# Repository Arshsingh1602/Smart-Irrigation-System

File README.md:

# Smart Irrigation System using LoRa and ESP32

This project is a transmitter-receiver duo using the LoRa communication protocol that helps us to revolutionize the agriculture industry by advancing the Smart Irrigation System. The transmitter acts as the node that transmits the data, and the receiver acts as the central node to receive that data and communicate it further, and process it.

Features of the project include: 
  1. Soil Moisture Detection
  2. Temperature and Humidity Detection
  3. Transmission (Long Range(upto 12-15km in rural areas))
  4. External parameters fetching, calculations, and predictions based on ML models
  5. Response to outcomes makes it a two-way system without human intervention.

| Component                 | Quantity | Description / Link         |
|---------------------------|----------|-----------------------------|
| ESP32 Dev Board           | 2        | WiFi + Bluetooth enabled    |
| SX1278 LoRa Module        | 2        | 433MHz                     |
| Soil Moisture Sensor      | 1        | Capacitive type            |
| MCP9808 Temp Sensor/DHT11 | 1        | Temperature sensor         |
| Water Valve (12V)         | 1        | Controlled via relay       |
| Relay Module              | 1        | For switching valve        |
| Power Supply (12V, 5V)    | 1 each   | For sensors and motors     |

To understand how the project works, we must understand some things first:

Soil Moisture Content: The amount of water present in the soil, usually measured as a percentage. It can be volumetric (by volume) or gravimetric (by weight).
Field Capacity (FC): The maximum moisture level that soil retains after excess water has drained. It represents the ideal moisture for plant growth.
Wilting Point (WP): The minimum moisture level at which plants begin to wilt due to lack of available water.
Permanent Wilting Point (PWP): A critical level where plants can no longer recover, even if water is reintroduced.
Available Water Content (AWC): The difference between field capacity and wilting point. It indicates the water range that plants can effectively use.

AWC = Field Capacity − Wilting Point

Saturation Point: When all soil pores are filled with water. Beyond this point, water drainage occurs, and root oxygen is limited.
Soil Water Potential (Tension): Indicates how tightly water is held in soil. Measured in kPa, where:

0 kPa = Saturated soil

−33 kPa ≈ Field capacity

−1500 kPa ≈ Wilting point

Soil Texture: Affects water retention. Sandy soils drain quickly, while clay holds more water.

The soil moisture sensor in the transmitter checks the water content in the soil, sends analogue data to the ESP 32, which takes the analogue data and converts it to scientifically accurate values and parameters. These parameters are defined above. There are various ways to program out AI/ML to find out what equation best fits the analogue data, which can be calculated based on heavy experimentation and data collection. The temperature sensor also sends its data to the ESP, and from there, the microcontroller takes the help of the LoRa module to transmit that data to the receiver that is kept far away from the transmitter. The main motto for this transmission is to have data collection and transmission from places in the field where the is no internet connection. One receiver can handle multiple transmitters varying from 4-10(max).

The receiver side is connected to the internet with wifi and can receive the transmitter data, and with the help of an internet connection, sends data to the cloud server that stores data according to the transmitter number, for further analysis. The main role of the receiver is to upload the transmitter's data and also send the data from the cloud back to the respective transmitters in order to control the relay, which controls the valve for irrigation. 

The ML model takes the temperature data and the soil moisture sensor, combined with the local humidity and rainfall fetched from the API. The model predicts when to command the specific valve to turn on, depending on the future rainfall predictions and the current status of the soil moisture. For example, if the soil moisture is below the critical level, then the part of the land should be irrigated immediately. But if the soil moisture is low, but the algorithm predicts that rainfall is expected in a few days, then, depending upon the average evaporation rate and the humidity, only a specific amount of water will be released such that the rainfall replenishes the remaining required amount. This way it saves water.

1. Connect all hardware as per the schematic.
2. Flash "sender.ino" to field ESP32.
3. Flash "receiver.ino" to the base ESP32.
4. Add your Firebase details to "firebase_config.h.h".
5. Power up both ESP32 boards.

Dependencies / Libraries:
- "Firebase_ESP_Client"
- "LoRa by Sandeep Mistry"

Challenges: 
  1. LoRa supports distances up to 15-20km in rural areas, but sometimes fields are larger than that.
  2. Theoretically, one transmitter can cover an area of 250 m^2, but this sample space technique that we assumed here only works for flat land.
  3. Configuring the patch of transmitters if farmers grow different types of crops on different patches of their land is difficult, as one crop can be selected but cannot select multiple crops.
  4. The single transmitter cannot handle so much data at the exact same time and will not upload correct data if we do so.

Future Scope:
  1. The individual transmitters can be coded as nodes of a mesh that can act like nodes that bounce/propel data forward if the distance between any transmitter and the receiver is too long.
  2. The receiver can be coded to generate a sequence of data received, store locally just for the purpose of uploading it to the server(forming a queue structure with the FIFO principle). This way, we can handle a huge amount of load on the receiver and avoid data corruption or system failure.
  3. Solar panels can be installed on each transmitter to make it self-sufficient.
  4. An algorithm can be developed that takes satellite images of the land from the maps API and analyzes the area based on terrain and slope, and finds the best locations to place our transmitters strategically to cover the whole field.

This is a public repo licensed under the MIT license. Users are obliged to reference/credit me(Arsh Singh) when copying the project or using/updating this project.

Made by Arsh Singh

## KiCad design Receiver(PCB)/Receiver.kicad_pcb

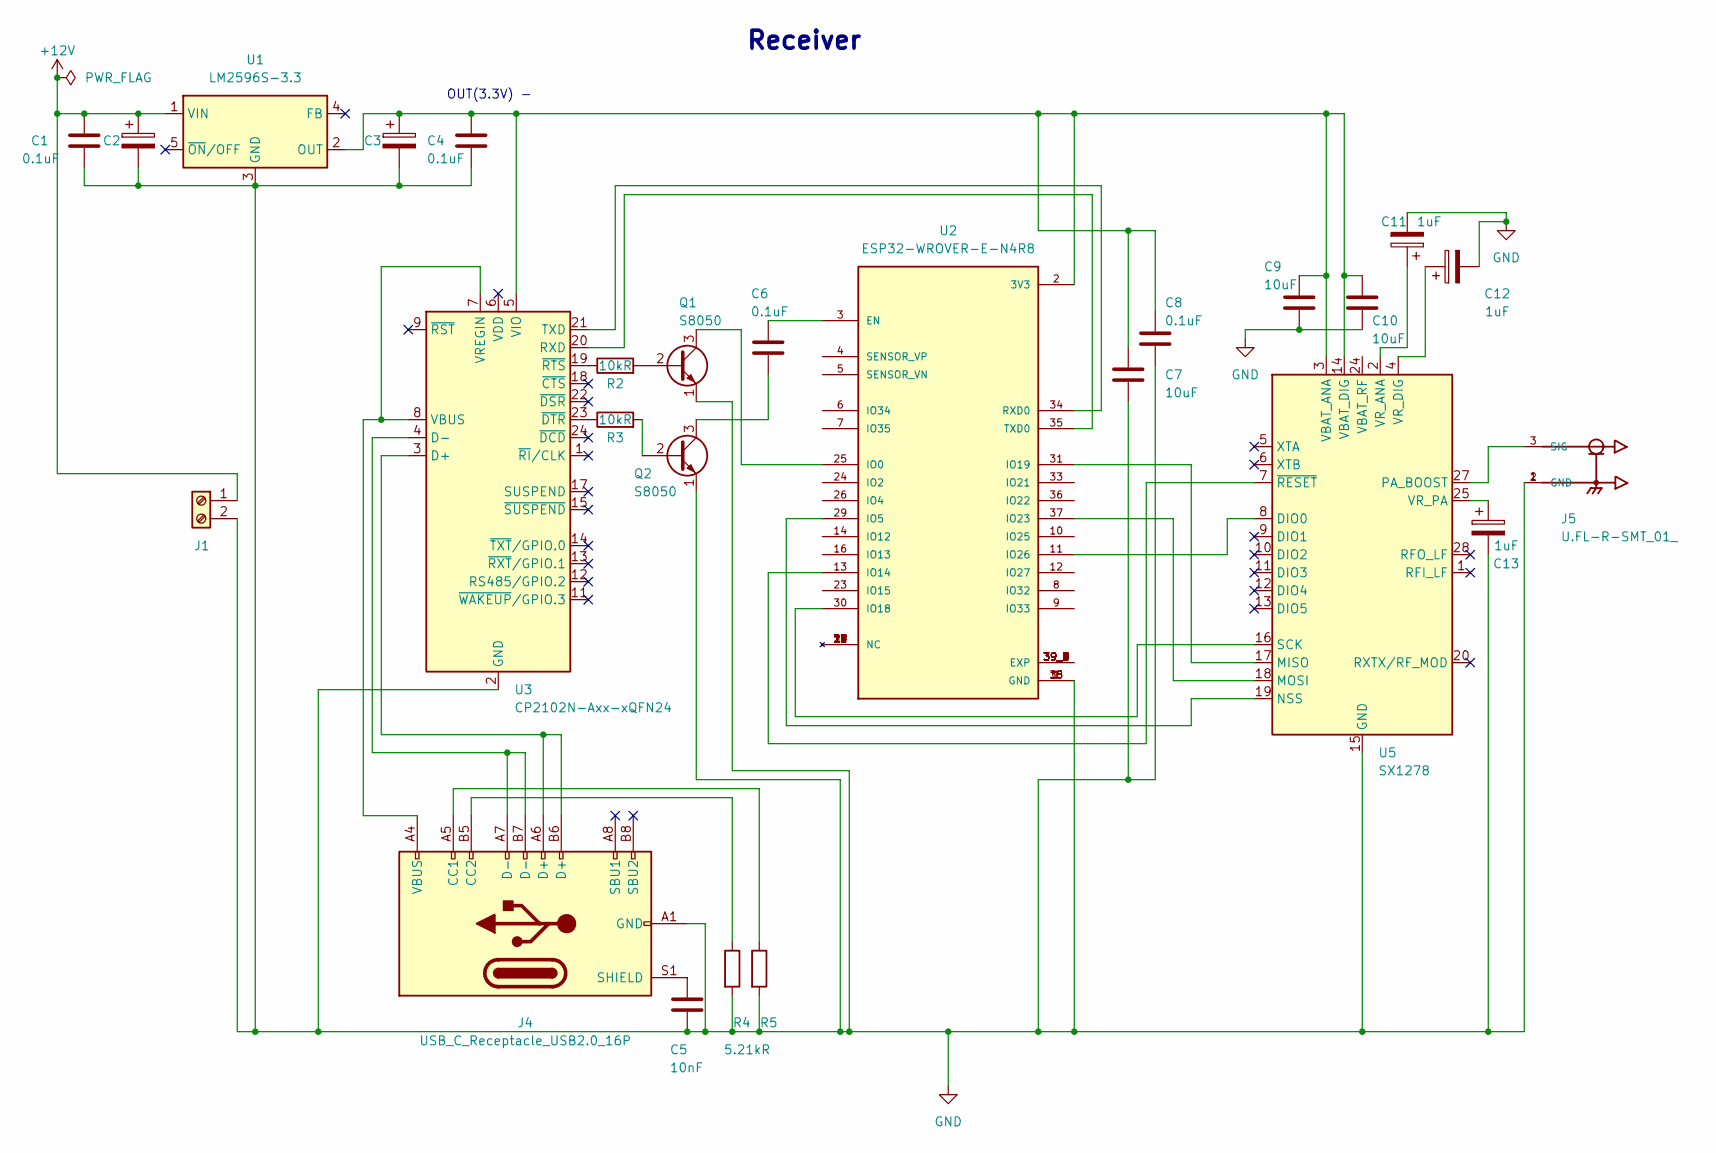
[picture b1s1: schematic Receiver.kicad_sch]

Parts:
C1, C4, C6, C8: 0.1uF; C_0603_1608Metric
C2, C3: 100uF; CP_Elec_3x5.3
C5: 10nF; C_0603_1608Metric_Pad1.08x0.95mm_HandSolder
C7, C9, C10: 10uF; C_0201_0603Metric_Pad0.64x0.40mm_HandSolder
C11: 1uF; C_0603_1608Metric_Pad1.08x0.95mm_HandSolder
C12, C13: 1uF; C_0805_2012Metric_Pad1.18x1.45mm_HandSolder
J1: Screw_Terminal_01x02; TerminalBlock_Phoenix_MPT-0,5-2-2.54_1x02_P2.54mm_Horizontal
J4: USB_C_Receptacle_USB2.0_16P; USB_C_Receptacle_GCT_USB4105-xx-A_16P_TopMnt_Horizontal
J5: U.FL-R-SMT_01_; HRS_U.FL-R-SMT_01_
Q1, Q2: S8050; TO-92_Inline
R2, R3: 10kR; C_0603_1608Metric_Pad1.08x0.95mm_HandSolder
R4, R5: 5.21kR; C_0603_1608Metric_Pad1.08x0.95mm_HandSolder
U1: LM2596S-3.3; TO-263-5_TabPin3
U2: ESP32-WROVER-E-N4R8; XCVR_ESP32-WROVER-E-N4R8; PARTREV 1.6
U3: CP2102N-Axx-xQFN24; QFN-24-1EP_4x4mm_P0.5mm_EP2.6x2.6mm
U5: SX1278; QFN-28-1EP_6x6mm_P0.65mm_EP4.8x4.8mm

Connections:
+12V: C1.1, C2.1, J1.1, U1.1 (VIN)
GND: C1.2, C2.2, C3.2, C4.2, C5.2, C7.2, C8.2, C9.2, C10.2, C11.2, C12.2, C13.2, J1.2, J4.A1 (GND), J4.A12 (GND), J4.B1 (GND), J4.B12 (GND), J5.1 (GND), J5.2 (GND), Q1.1 (E), Q2.1 (E), R4.2, R5.2, U1.3 (GND), U2.1 (GND), U2.15 (GND), U2.38 (GND), U3.2 (GND), U3.25 (GND), U5.15 (GND), U5.21 (GND), U5.22 (GND), U5.23 (GND), U5.26 (GND), U5.29 (GND)
unnamed: J4.A5 (CC1), R5.1
unnamed: J4.B5 (CC2), R4.1
unnamed: C5.1, J4.S1 (SHIELD)
unnamed: J5.3 (SIG), U5.27 (PA_BOOST)
unnamed: Q1.2 (B), R2.2
unnamed: Q1.3 (C), U2.25 (IO0)
unnamed: Q2.2 (B), R3.2
unnamed: C6.2, Q2.3 (C)
unnamed: C3.1, C4.1, C7.1, C8.1, C9.1, C10.1, U1.2 (OUT), U2.2 (3V3), U3.5 (VIO), U5.3 (VBAT_ANA), U5.14 (VBAT_DIG)
unnamed: C6.1, U2.3 (EN)
unnamed: U2.39_1 (EXP), U2.39_2 (EXP), U2.39_3 (EXP), U2.39_4 (EXP), U2.39_5 (EXP), U2.39_6 (EXP), U2.39_7 (EXP), U2.39_8 (EXP), U2.39_9 (EXP)
unnamed: U2.29 (IO5), U5.19 (NSS)
unnamed: U2.13 (IO14), U5.7 (~RESET)
unnamed: U2.30 (IO18), U5.16 (SCK)
unnamed: U2.31 (IO19), U5.17 (MISO)
unnamed: U2.37 (IO23), U5.18 (MOSI)
unnamed: U2.11 (IO26), U5.8 (DIO0)
unnamed: U2.34 (RXD0), U3.21 (TXD)
unnamed: U2.35 (TXD0), U3.20 (RXD)
unnamed: J4.A6 (D+), J4.B6 (D+), U3.3 (D+)
unnamed: J4.A7 (D-), J4.B7 (D-), U3.4 (D-)
unnamed: J4.A4 (VBUS), J4.A9 (VBUS), J4.B4 (VBUS), J4.B9 (VBUS), U3.7 (VREGIN), U3.8 (VBUS)
unnamed: R3.1, U3.23 (~DTR)
unnamed: R2.1, U3.19 (~RTS)
unnamed: C11.1, U5.2 (VR_ANA)
unnamed: C12.1, U5.4 (VR_DIG)
unnamed: C13.1, U5.25 (VR_PA)

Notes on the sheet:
Receiver
OUT(3.3V) -

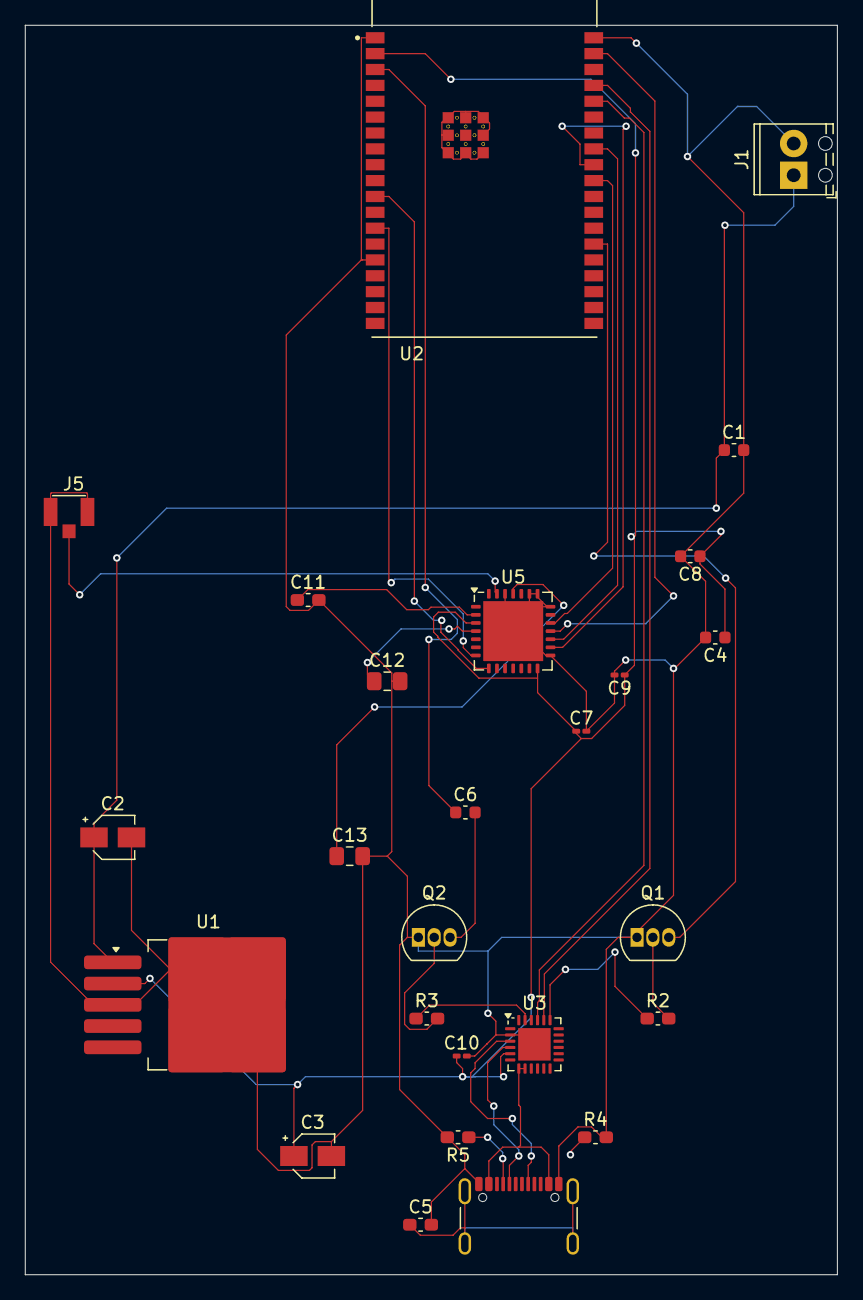
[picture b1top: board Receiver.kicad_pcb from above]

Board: 2 copper layers, 65.0 x 100.0 mm, 26 parts (0 on the bottom side), 29 nets.

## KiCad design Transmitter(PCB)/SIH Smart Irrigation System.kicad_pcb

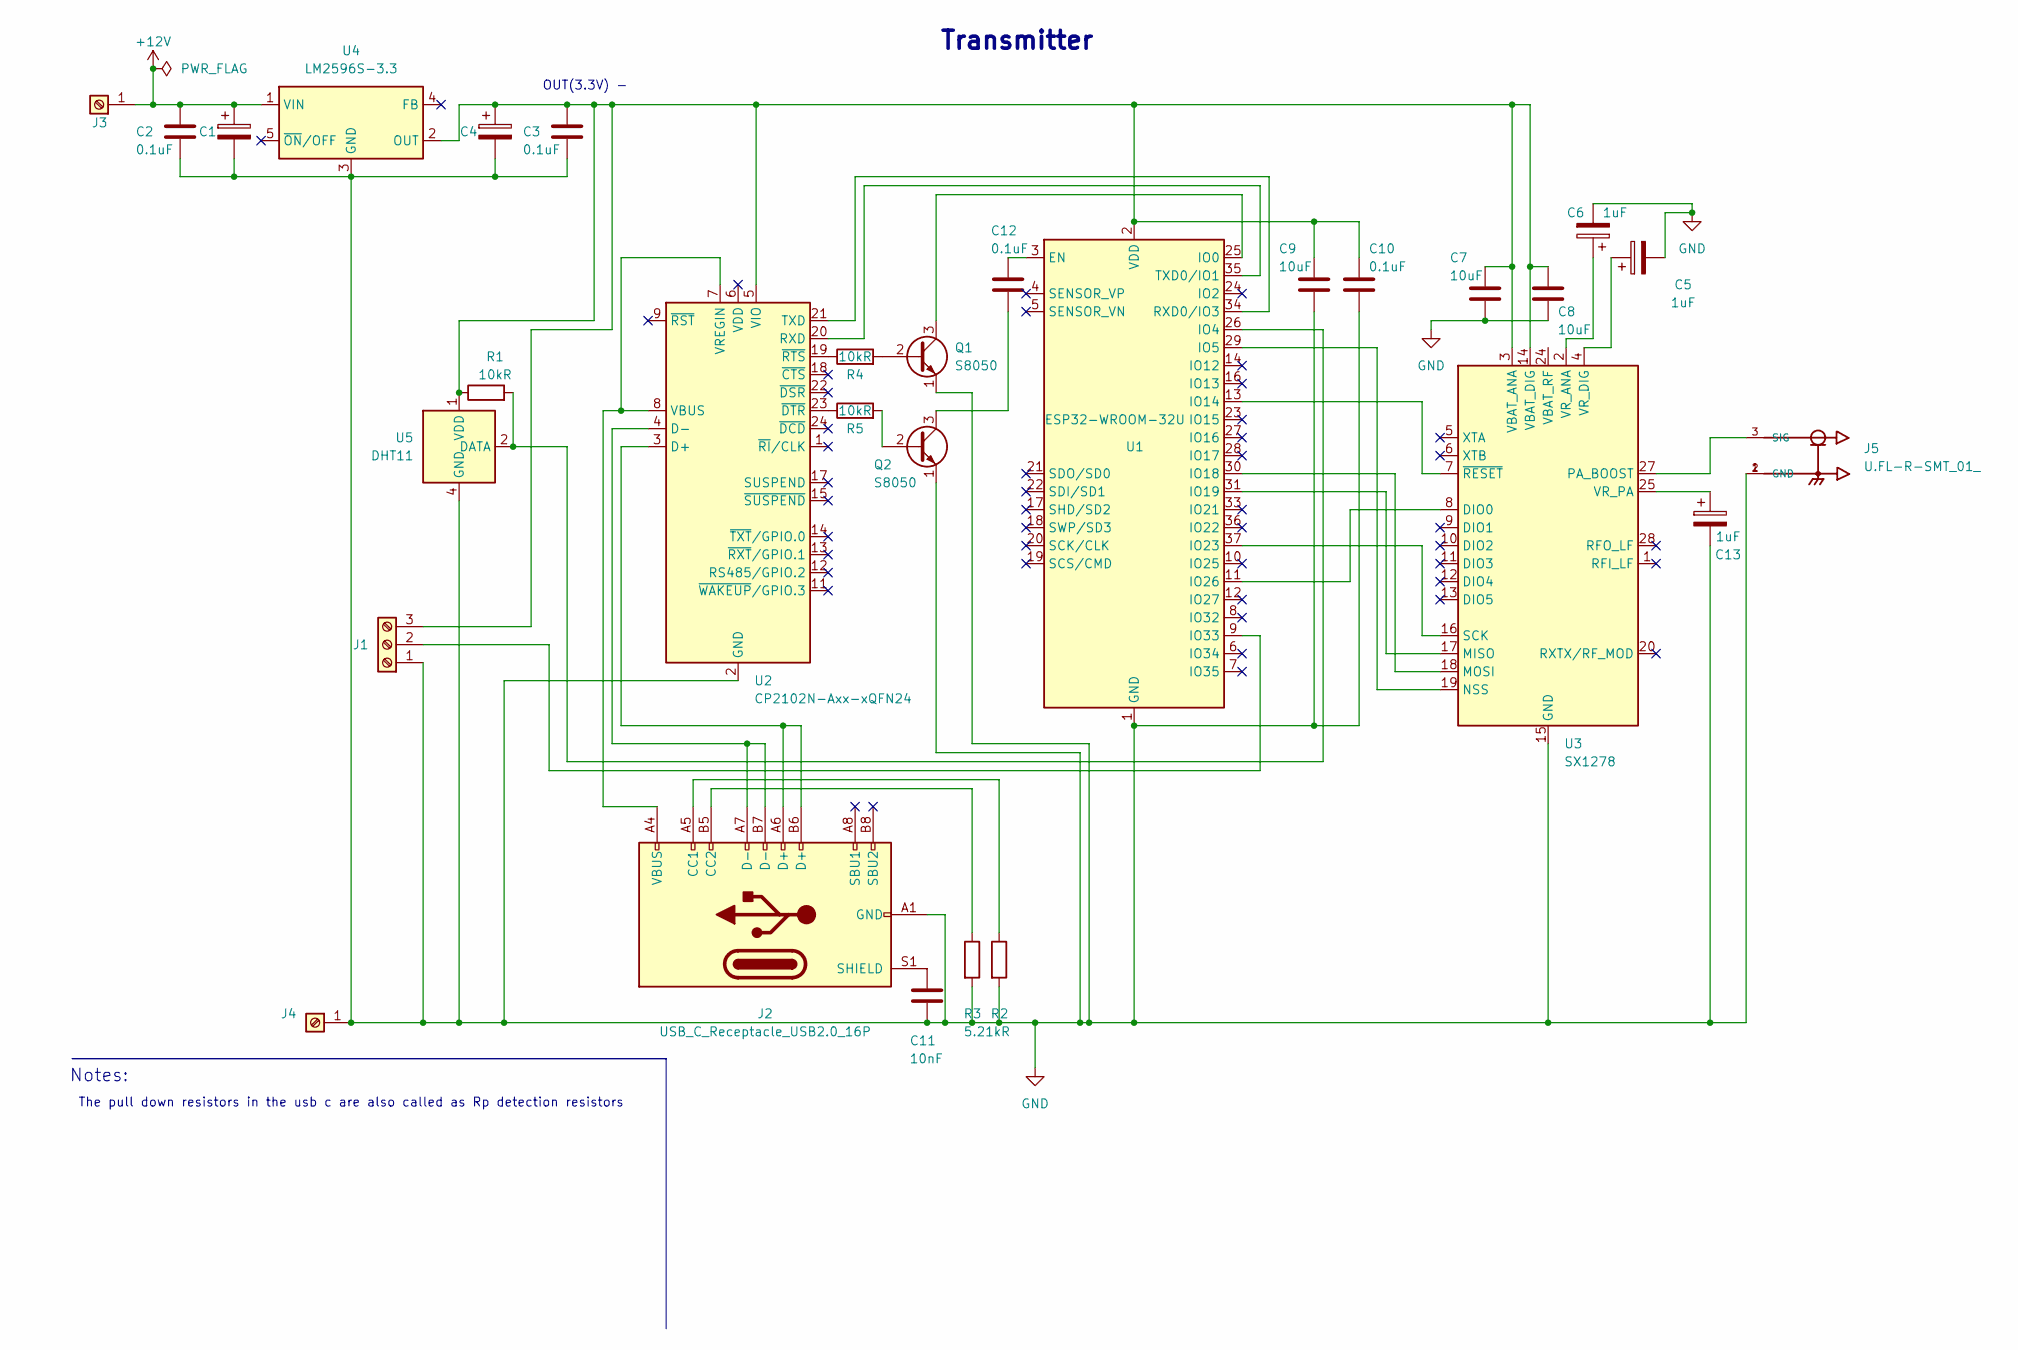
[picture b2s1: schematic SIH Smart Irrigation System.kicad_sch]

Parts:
C1, C4: 100uF; CP_Elec_3x5.3
C2, C3, C10, C12: 0.1uF; C_0603_1608Metric
C5, C13: 1uF; C_0805_2012Metric_Pad1.18x1.45mm_HandSolder
C6: 1uF; C_0603_1608Metric_Pad1.08x0.95mm_HandSolder
C7, C8, C9: 10uF; C_0201_0603Metric_Pad0.64x0.40mm_HandSolder
C11: 10nF; C_0603_1608Metric_Pad1.08x0.95mm_HandSolder
J1: Screw_Terminal_01x03; TerminalBlock_Phoenix_MKDS-3-3-5.08_1x03_P5.08mm_Horizontal
J2: USB_C_Receptacle_USB2.0_16P; USB_C_Receptacle_GCT_USB4105-xx-A_16P_TopMnt_Horizontal
J3, J4: Screw_Terminal_01x01; TerminalBlock_MetzConnect_360271_1x01_Horizontal_ScrewM3.0_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
J5: U.FL-R-SMT_01_; HRS_U.FL-R-SMT_01_
Q1, Q2: S8050; TO-92_Inline
R1, R4, R5: 10kR; C_0603_1608Metric_Pad1.08x0.95mm_HandSolder
R2, R3: 5.21kR; C_0603_1608Metric_Pad1.08x0.95mm_HandSolder
U1: ESP32-WROOM-32U
U2: CP2102N-Axx-xQFN24; QFN-24-1EP_4x4mm_P0.5mm_EP2.6x2.6mm
U3: SX1278; QFN-28-1EP_6x6mm_P0.65mm_EP4.8x4.8mm
U4: LM2596S-3.3; TO-263-5_TabPin3
U5: DHT11; Aosong_DHT11_5.5x12.0_P2.54mm

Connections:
+12V: C1.1, C2.1, J3.1, U4.1 (VIN)
GND: C1.2, C2.2, C3.2, C4.2, C5.2, C6.2, C7.2, C8.2, C9.2, C10.2, C11.2, C13.2, J1.1, J2.A1 (GND), J2.A12 (GND), J2.B1 (GND), J2.B12 (GND), J4.1, J5.1 (GND), J5.2 (GND), Q1.1 (E), Q2.1 (E), R2.2, R3.2, U1.1 (GND), U1.15 (GND), U1.38 (GND), U1.39 (GND), U2.2 (GND), U2.25 (GND), U3.15 (GND), U3.21 (GND), U3.22 (GND), U3.23 (GND), U3.26 (GND), U3.29 (GND), U4.3 (GND), U5.4 (GND)
unnamed: J1.2, U1.9 (IO33)
unnamed: C3.1, C4.1, C7.1, C8.1, C9.1, C10.1, J1.3, R1.1, U1.2 (VDD), U2.5 (VIO), U3.3 (VBAT_ANA), U3.14 (VBAT_DIG), U4.2 (OUT), U5.1 (VDD)
unnamed: J2.A5 (CC1), R2.1
unnamed: J2.B5 (CC2), R3.1
unnamed: C11.1, J2.S1 (SHIELD)
unnamed: J5.3 (SIG), U3.27 (PA_BOOST)
unnamed: Q1.2 (B), R4.2
unnamed: Q1.3 (C), U1.25 (IO0)
unnamed: Q2.2 (B), R5.2
unnamed: C12.2, Q2.3 (C)
unnamed: C12.1, U1.3 (EN)
unnamed: R1.2, U1.26 (IO4), U5.2 (DATA)
unnamed: U1.29 (IO5), U3.19 (NSS)
unnamed: U1.13 (IO14), U3.7 (~RESET)
unnamed: U1.30 (IO18), U3.18 (MOSI)
unnamed: U1.31 (IO19), U3.17 (MISO)
unnamed: U1.37 (IO23), U3.16 (SCK)
unnamed: U1.11 (IO26), U3.8 (DIO0)
unnamed: U1.34 (RXD0/IO3), U2.21 (TXD)
unnamed: U1.35 (TXD0/IO1), U2.20 (RXD)
unnamed: J2.A6 (D+), J2.B6 (D+), U2.3 (D+)
unnamed: J2.A7 (D-), J2.B7 (D-), U2.4 (D-)
unnamed: J2.A4 (VBUS), J2.A9 (VBUS), J2.B4 (VBUS), J2.B9 (VBUS), U2.7 (VREGIN), U2.8 (VBUS)
unnamed: R5.1, U2.23 (~DTR)
unnamed: R4.1, U2.19 (~RTS)
unnamed: C6.1, U3.2 (VR_ANA)
unnamed: C5.1, U3.4 (VR_DIG)
unnamed: C13.1, U3.25 (VR_PA)

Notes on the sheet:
Notes:
Transmitter
The pull down resistors in the usb c are also called as Rp detection resistors
OUT(3.3V) -

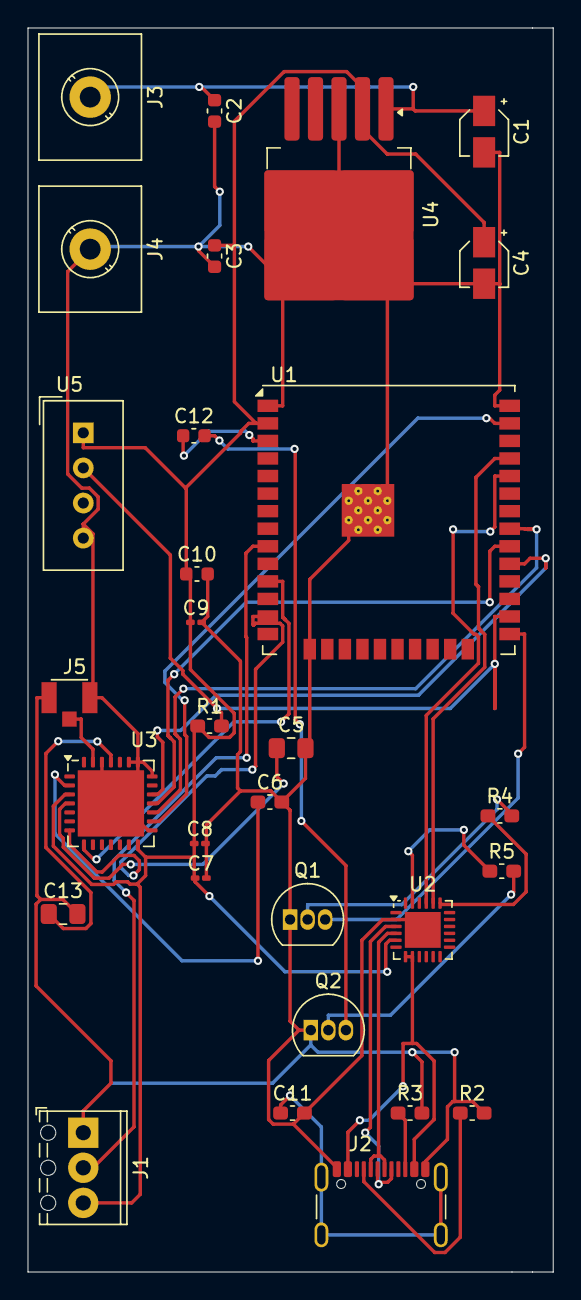
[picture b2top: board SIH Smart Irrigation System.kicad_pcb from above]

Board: 2 copper layers, 38.0 x 90.0 mm, 30 parts (0 on the bottom side), 30 nets.

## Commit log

2024-12-20 Initial commit for Receiver
2024-12-20 Initial Transmitter commit
2025-07-24 Create LICENSE
2025-07-24 Uploaded Images
2025-07-24 Pushed Transmitter PCB and Schema
2025-08-03 Added Receiver PCB
